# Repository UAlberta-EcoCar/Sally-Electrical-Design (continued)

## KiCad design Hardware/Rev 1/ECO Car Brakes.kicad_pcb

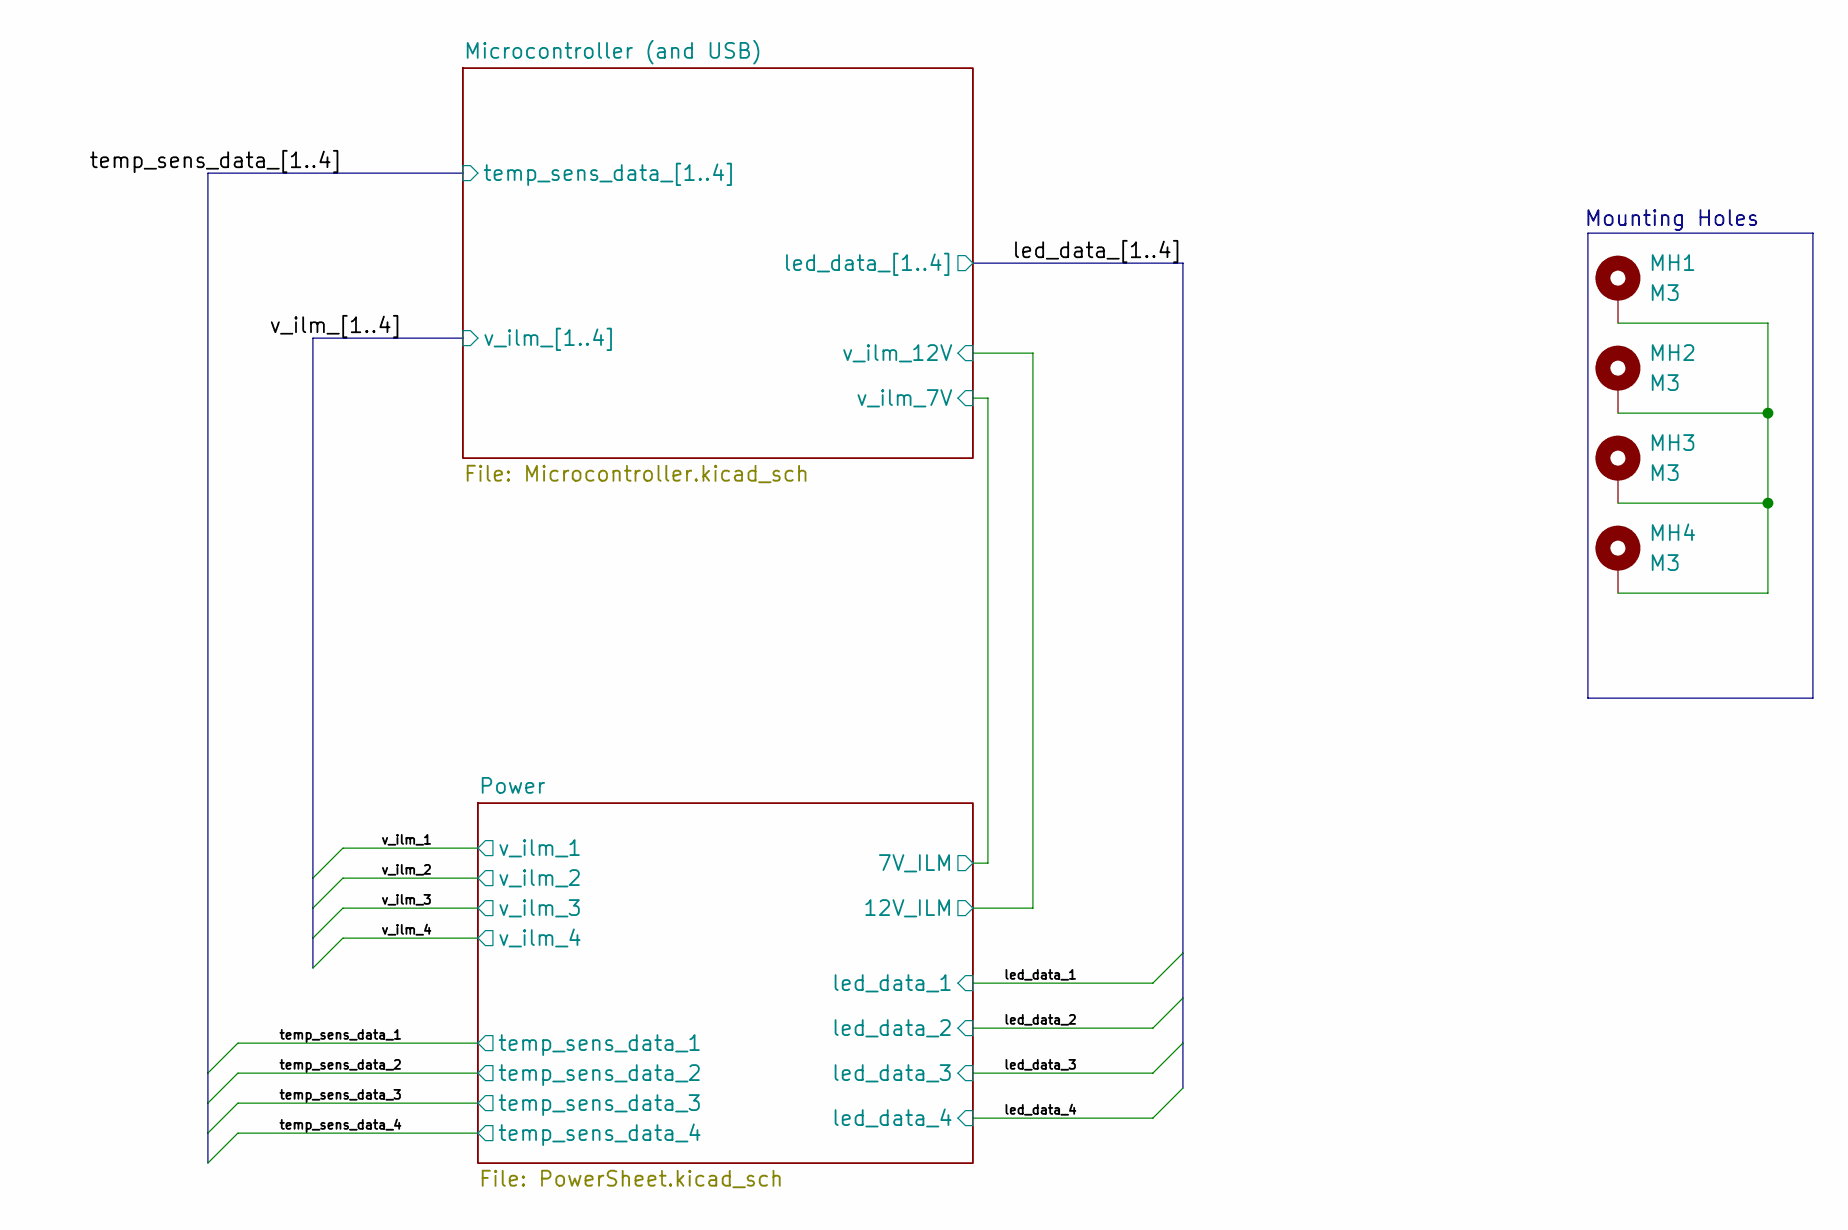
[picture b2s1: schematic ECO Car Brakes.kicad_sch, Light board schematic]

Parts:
MH1, MH2, MH3, MH4: M3; MountingHole_3.2mm_M3_Pad_Via

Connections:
unnamed: MH1.1 (1_1), MH2.1 (1_1), MH3.1 (1_1), MH4.1 (1_1)

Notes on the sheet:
Mounting Holes

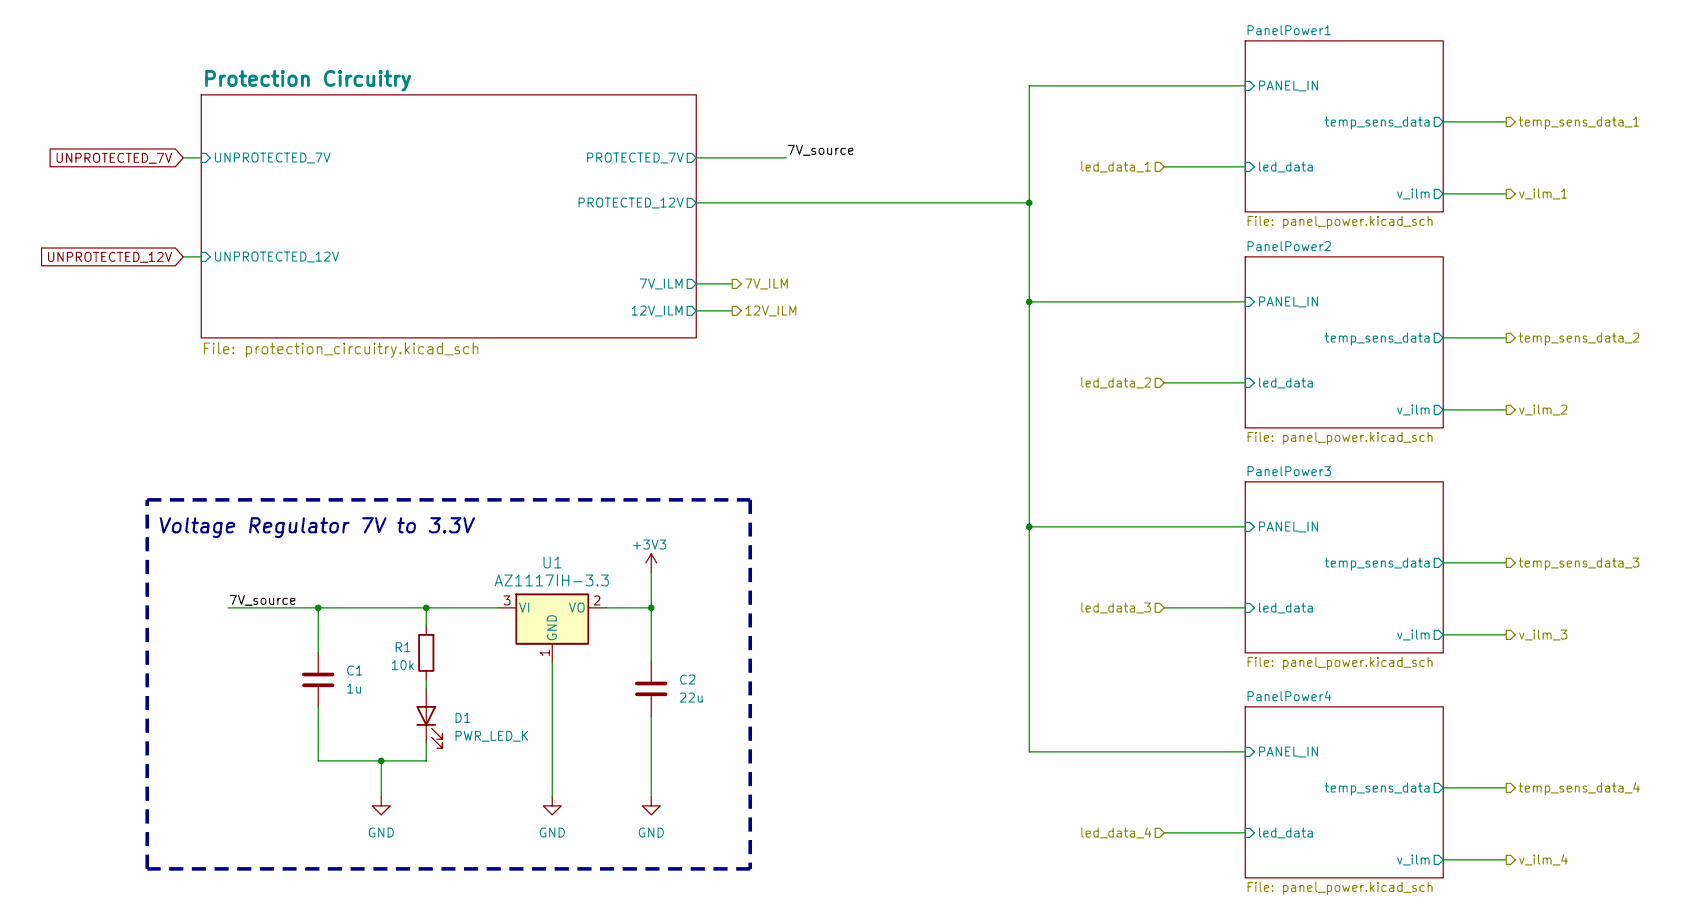
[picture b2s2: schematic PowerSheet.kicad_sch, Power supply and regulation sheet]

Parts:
C1: 1u; C_0603_1608Metric
C2: 22u; C_0603_1608Metric
D1: PWR_LED_K; LED_0805_2012Metric
R1: 10k; R_0603_1608Metric
U1: AZ1117IH-3.3; SOT-223-3_TabPin2

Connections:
+3V3: C2.1, U1.2 (VO); also elsewhere on the board
/Power/7V_source: C1.1, R1.2, U1.3 (VI); also elsewhere on the board
GND: C1.2, C2.2, D1.1 (K), U1.1 (GND); also elsewhere on the board
unnamed: D1.2 (A), R1.1

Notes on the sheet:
Voltage Regulator 7V to 3.3V

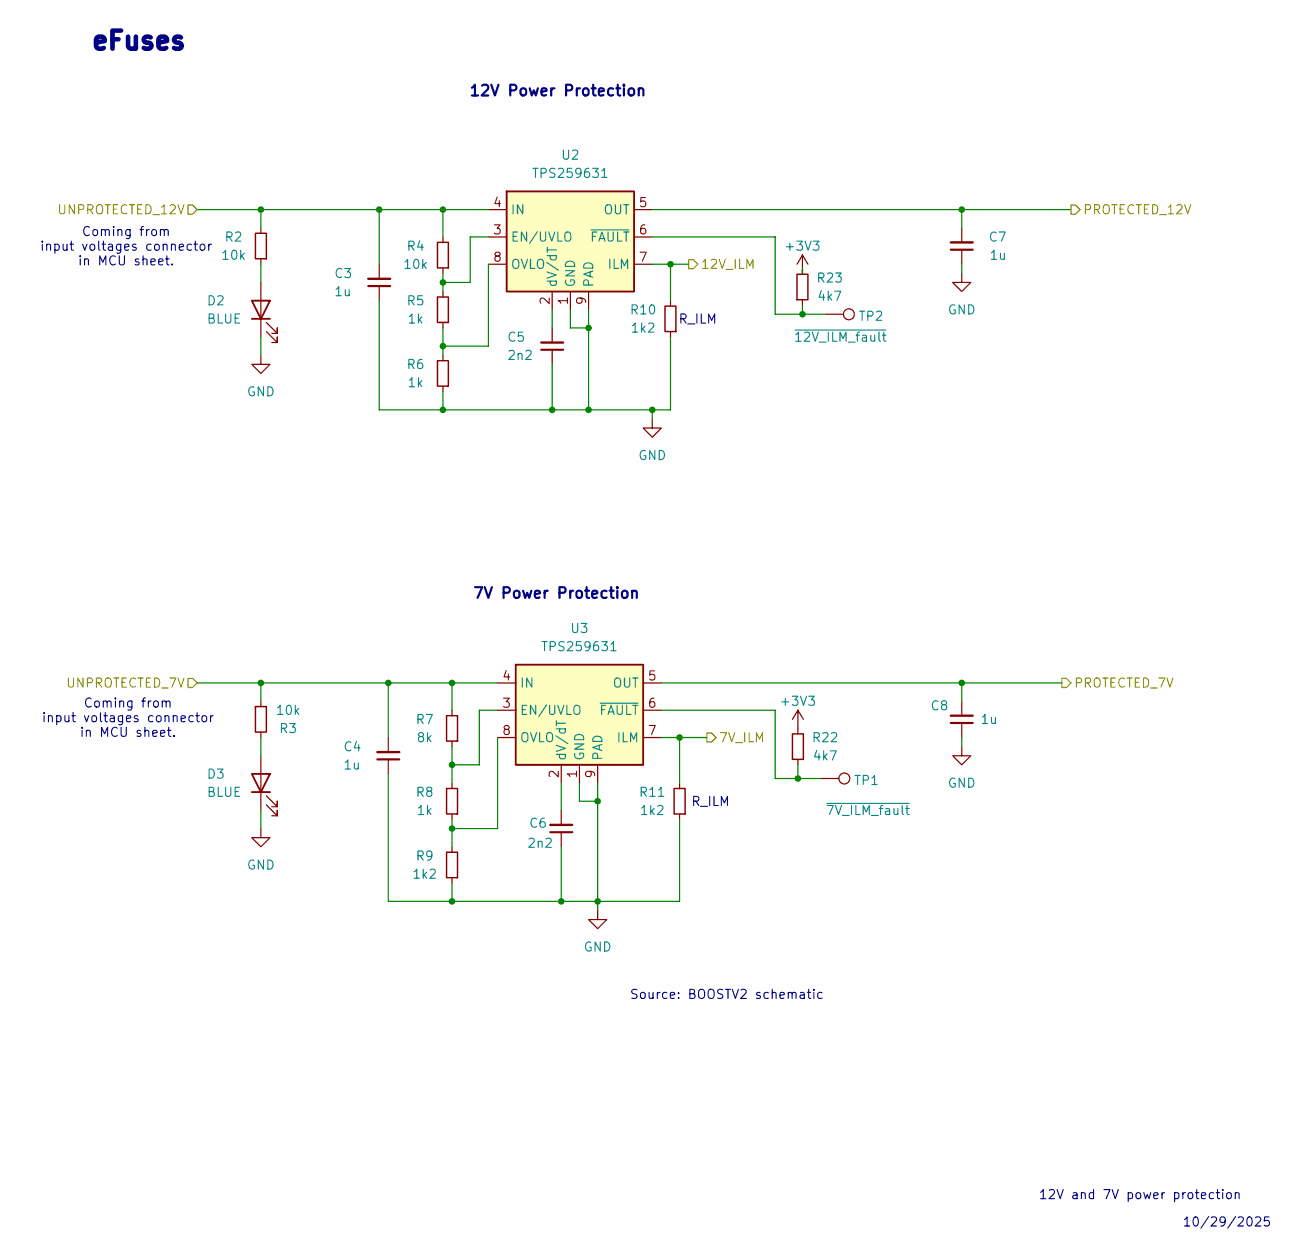
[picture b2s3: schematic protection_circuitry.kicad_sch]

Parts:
C3, C4, C7, C8: 1u; C_0603_1608Metric; Part# C15849
C5, C6: 2n2; C_0603_1608Metric; Part# C1604
D2, D3: BLUE; LED_0805_2012Metric; Part# C72041
R2: 10k; R_0603_1608Metric; Part# C23253
R3: 10k; R_0603_1608Metric; Part# C22966
R4: 10k; R_0603_1608Metric
R5, R6, R8: 1k; R_0603_1608Metric
R7: 8k; R_0603_1608Metric
R9, R10, R11: 1k2; R_0603_1608Metric
R22, R23: 4k7; R_0603_1608Metric
TP1: ~{7V_ILM_fault}; TestPoint_Pad_2.0x2.0mm
TP2: ~{12V_ILM_fault}; TestPoint_Pad_2.0x2.0mm
U2, U3: TPS259631; TI_SO-PowerPAD-8

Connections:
+3V3: R22.2, R23.2; also elsewhere on the board
/Microcontroller (and USB)/v_ilm_7V: R11.2, U3.7 (ILM); also elsewhere on the board
/Microcontroller (and USB)/v_ilm_12V: R10.2, U2.7 (ILM); also elsewhere on the board
/Power/7V_source: C8.2, U3.5 (OUT); also elsewhere on the board
/Power/PanelPower1/PANEL_IN: C7.2, U2.5 (OUT); also elsewhere on the board
GND: C3.1, C4.1, C5.1, C6.1, C7.1, C8.1, D2.1 (K), D3.1 (K), R6.1, R9.1, R10.1, R11.1, U2.1 (GND), U2.9 (PAD), U3.1 (GND), U3.9 (PAD); also elsewhere on the board
unnamed: D2.2 (A), R2.1
unnamed: D3.2 (A), R3.2
unnamed: R4.1, R5.2, U2.3 (EN/UVLO)
unnamed: R5.1, R6.2, U2.8 (OVLO)
unnamed: C5.2, U2.2 (dV/dT)
unnamed: R23.1, TP2.1 (1_1), U2.6 (~FAULT)
unnamed: R7.1, R8.2, U3.3 (EN/UVLO)
unnamed: R8.1, R9.2, U3.8 (OVLO)
unnamed: C6.2, U3.2 (dV/dT)
unnamed: R22.1, TP1.1 (1_1), U3.6 (~FAULT)
UNPROTECTED_7V: C4.2, R3.1, R7.2, U3.4 (IN); also elsewhere on the board
UNPROTECTED_12V: C3.2, R2.2, R4.2, U2.4 (IN); also elsewhere on the board

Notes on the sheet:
10/29/2025
R_ILM
eFuses
12V Power Protection
Coming from input voltages connector in MCU sheet.
12V and 7V power protection
Source: BOOSTV2 schematic
7V Power Protection

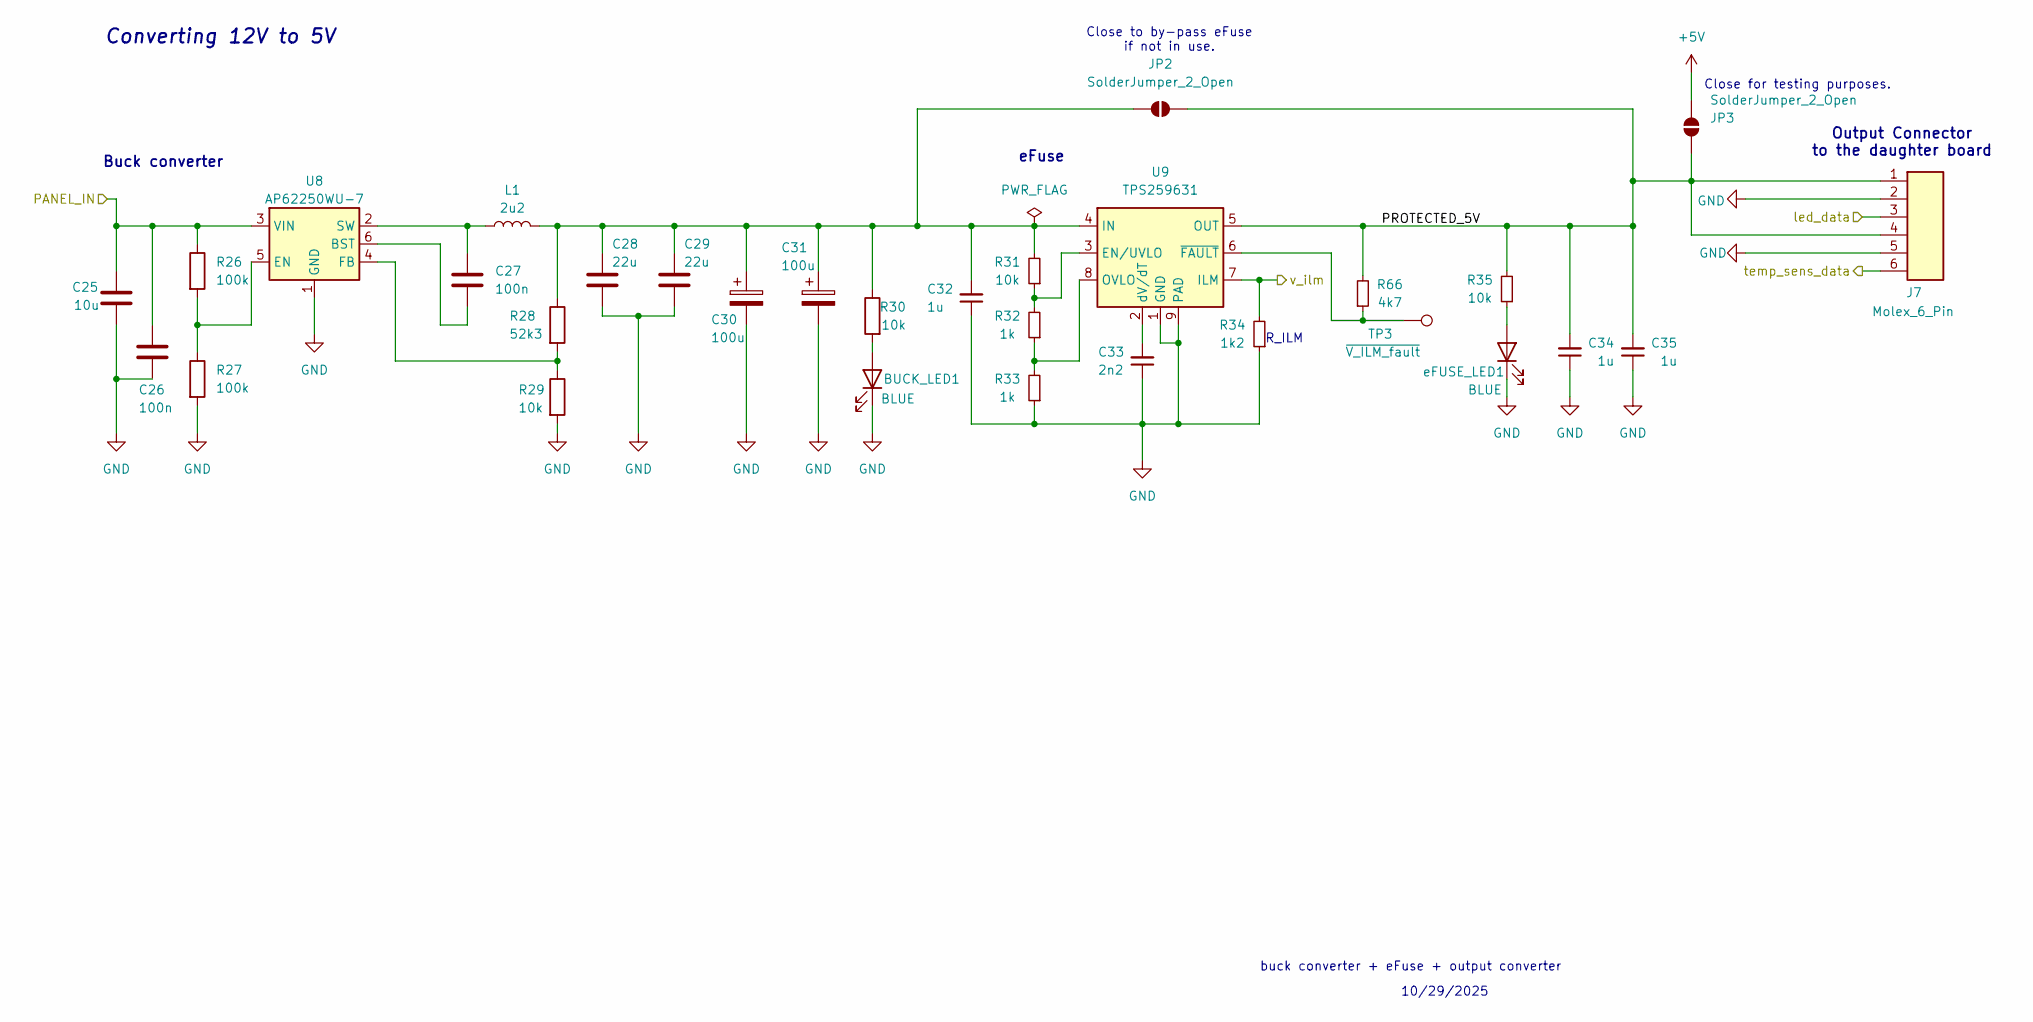
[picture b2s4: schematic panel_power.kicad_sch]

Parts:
BUCK_LED1: BLUE; LED_0805_2012Metric; Digikey # 160-1647-1-ND
C25: 10u; C_0603_1608Metric
C26, C27: 100n; C_0603_1608Metric; Digikey # CC0603KRX7R7BB104
C28, C29: 22u; C_0603_1608Metric
C30, C31: 100u; CP_Elec_6.3x7.7; Digikey # P10387TB-ND
C32, C34, C35: 1u; C_0603_1608Metric; Part# C15849
C33: 2n2; C_0603_1608Metric; Part# C1604
J7: Molex_6_Pin; Molex_6_Pin_FTP
JP2, JP3: SolderJumper_2_Open; SolderJumper-2_P1.3mm_Open_RoundedPad1.0x1.5mm
L1: 2u2; L_0603_1608Metric; Digikey # 732-13496-1-ND
R26, R27: 100k; R_0603_1608Metric
R28: 52k3; R_0603_1608Metric; Digikey # RMCF0603FT52K3CT-ND
R29: 10k; R_0603_1608Metric; Digikey # RMCF0603FT52K3CT-ND
R30: 10k; R_0603_1608Metric; JLCPCB Part#(Optional) C28636
R31: 10k; R_0603_1608Metric
R32, R33: 1k; R_0603_1608Metric
R34: 1k2; R_0603_1608Metric
R35: 10k; R_0603_1608Metric; Part# C23253
R66: 4k7; R_0603_1608Metric
TP3: ~{V_ILM_fault}; TestPoint_Pad_2.0x2.0mm
U8: AP62250WU-7; TSOT-23-6
U9: TPS259631; TI_SO-PowerPAD-8
eFUSE_LED1: BLUE; LED_0805_2012Metric; Part# C72041

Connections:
+5V: JP3.2 (B); also elsewhere on the board
/Power/PanelPower1/PANEL_IN: C25.1, C26.1, R26.1, U8.3 (VIN); also elsewhere on the board
/Power/PanelPower1/PROTECTED_5V: C34.2, C35.2, J7.1, J7.4, JP2.2 (B), JP3.1 (A), R35.2, R66.2, U9.5 (OUT)
/led_data_1: J7.3; also elsewhere on the board
/temp_sens_data_1: J7.6; also elsewhere on the board
/v_ilm_1: R34.2, U9.7 (ILM); also elsewhere on the board
GND: BUCK_LED1.1 (K), C25.2, C26.2, C28.2, C29.2, C30.2, C31.2, C32.1, C33.1, C34.1, C35.1, J7.2, J7.5, R27.2, R29.2, R33.1, R34.1, U8.1 (GND), U9.1 (GND), U9.9 (PAD), eFUSE_LED1.1 (K); also elsewhere on the board
unnamed 45: R30.2; also elsewhere on the board
unnamed: C28.1, C29.1, C30.1, C31.1, C32.2, JP2.1 (A), L1.2, R28.1, R30.1, R31.2, U9.4 (IN)
unnamed: C27.2, U8.6 (BST)
unnamed: R26.2, R27.1, U8.5 (EN)
unnamed: R28.2, R29.1, U8.4 (FB)
unnamed: C27.1, L1.1, U8.2 (SW)
unnamed: R31.1, R32.2, U9.3 (EN/UVLO)
unnamed: R32.1, R33.2, U9.8 (OVLO)
unnamed: C33.2, U9.2 (dV/dT)
unnamed: R66.1, TP3.1 (1_1), U9.6 (~FAULT)
unnamed: R35.1, eFUSE_LED1.2 (A)

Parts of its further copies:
C36, C47, C58: 10u; C_0603_1608Metric
C37, C38, C48, C49, C59, C60: 100n; C_0603_1608Metric; Digikey # CC0603KRX7R7BB104
C39, C40, C50, C51, C61, C62: 22u; C_0603_1608Metric
C41, C42, C52, C53, C63, C64: 100u; CP_Elec_6.3x7.7; Digikey # P10387TB-ND
C43, C45, C46, C54, C56, C57, C65, C67, C68: 1u; C_0603_1608Metric; Part# C15849
C44, C55, C66: 2n2; C_0603_1608Metric; Part# C1604
J8, J9, J10: Molex_6_Pin; Molex_6_Pin_FTP
JP4, JP5, JP6, JP7, JP8, JP9: SolderJumper_2_Open; SolderJumper-2_P1.3mm_Open_RoundedPad1.0x1.5mm
L2, L3, L4: 2u2; L_0603_1608Metric; Digikey # 732-13496-1-ND
R36, R37, R46, R47, R56, R57: 100k; R_0603_1608Metric
R38, R48, R58: 52k3; R_0603_1608Metric; Digikey # RMCF0603FT52K3CT-ND
R39, R49, R59: 10k; R_0603_1608Metric; Digikey # RMCF0603FT52K3CT-ND
R40, R50, R60: 10k; R_0603_1608Metric; JLCPCB Part#(Optional) C28636
R41, R51, R61: 10k; R_0603_1608Metric
R42, R43, R52, R53, R62, R63: 1k; R_0603_1608Metric
R44, R54, R64: 1k2; R_0603_1608Metric
R45, R55, R65: 10k; R_0603_1608Metric; Part# C23253
R67, R68, R69: 4k7; R_0603_1608Metric
TP4, TP5, TP6: ~{V_ILM_fault}; TestPoint_Pad_2.0x2.0mm
U10, U12, U14: AP62250WU-7; TSOT-23-6
U11, U13, U15: TPS259631; TI_SO-PowerPAD-8
eFUSE_LED2: BLUE; LED_0805_2012Metric; Part# C72041

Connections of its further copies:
+5V: JP5.2 (B), JP7.2 (B), JP9.2 (B); also elsewhere on the board
/Power/PanelPower1/PANEL_IN: C36.1, C37.1, C47.1, C48.1, C58.1, C59.1, R36.1, R46.1, R56.1, U10.3 (VIN), U12.3 (VIN), U14.3 (VIN); also elsewhere on the board
/Power/PanelPower2/PROTECTED_5V: C45.2, C46.2, J8.1, J8.4, JP4.2 (B), JP5.1 (A), R45.2, R67.2, U11.5 (OUT)
/Power/PanelPower3/PROTECTED_5V: C56.2, C57.2, J9.1, J9.4, JP6.2 (B), JP7.1 (A), R55.2, R68.2, U13.5 (OUT)
/Power/PanelPower4/PROTECTED_5V: C67.2, C68.2, J10.1, J10.4, JP8.2 (B), JP9.1 (A), R65.2, R69.2, U15.5 (OUT)
/led_data_2: J8.3; also elsewhere on the board
/led_data_3: J9.3; also elsewhere on the board
/led_data_4: J10.3; also elsewhere on the board
/temp_sens_data_2: J8.6; also elsewhere on the board
/temp_sens_data_3: J9.6; also elsewhere on the board
/temp_sens_data_4: J10.6; also elsewhere on the board
/v_ilm_2: R44.2, U11.7 (ILM); also elsewhere on the board
/v_ilm_3: R54.2, U13.7 (ILM); also elsewhere on the board
/v_ilm_4: R64.2, U15.7 (ILM); also elsewhere on the board
GND: C36.2, C37.2, C39.2, C40.2, C41.2, C42.2, C43.1, C44.1, C45.1, C46.1, C47.2, C48.2, C50.2, C51.2, C52.2, C53.2, C54.1, C55.1, C56.1, C57.1, C58.2, C59.2, C61.2, C62.2, C63.2, C64.2, C65.1, C66.1, C67.1, C68.1, J8.2, J8.5, J9.2, J9.5, J10.2, J10.5, R37.2, R39.2, R43.1, R44.1, R47.2, R49.2, R53.1, R54.1, R57.2, R59.2, R63.1, R64.1, U10.1 (GND), U11.1 (GND), U11.9 (PAD), U12.1 (GND), U13.1 (GND), U13.9 (PAD), U14.1 (GND), U15.1 (GND), U15.9 (PAD), eFUSE_LED2.1 (K); also elsewhere on the board
unnamed 46: R40.2; also elsewhere on the board
unnamed 47: R50.2; also elsewhere on the board
unnamed 48: R60.2; also elsewhere on the board
unnamed: C39.1, C40.1, C41.1, C42.1, C43.2, JP4.1 (A), L2.2, R38.1, R40.1, R41.2, U11.4 (IN)
unnamed: C50.1, C51.1, C52.1, C53.1, C54.2, JP6.1 (A), L3.2, R48.1, R50.1, R51.2, U13.4 (IN)
unnamed: C61.1, C62.1, C63.1, C64.1, C65.2, JP8.1 (A), L4.2, R58.1, R60.1, R61.2, U15.4 (IN)
unnamed: C38.2, U10.6 (BST)
unnamed: R36.2, R37.1, U10.5 (EN)
unnamed: R38.2, R39.1, U10.4 (FB)
unnamed: C38.1, L2.1, U10.2 (SW)
unnamed: R41.1, R42.2, U11.3 (EN/UVLO)
unnamed: R42.1, R43.2, U11.8 (OVLO)
unnamed: C44.2, U11.2 (dV/dT)
unnamed: R67.1, TP4.1 (1_1), U11.6 (~FAULT)
unnamed: C49.2, U12.6 (BST)
unnamed: R46.2, R47.1, U12.5 (EN)
unnamed: R48.2, R49.1, U12.4 (FB)
unnamed: C49.1, L3.1, U12.2 (SW)
unnamed: R51.1, R52.2, U13.3 (EN/UVLO)
unnamed: R52.1, R53.2, U13.8 (OVLO)
unnamed: C55.2, U13.2 (dV/dT)
unnamed: R68.1, TP5.1 (1_1), U13.6 (~FAULT)
unnamed: C60.2, U14.6 (BST)
unnamed: R56.2, R57.1, U14.5 (EN)
unnamed: R58.2, R59.1, U14.4 (FB)
unnamed: C60.1, L4.1, U14.2 (SW)
unnamed: R61.1, R62.2, U15.3 (EN/UVLO)
unnamed: R62.1, R63.2, U15.8 (OVLO)
unnamed: C66.2, U15.2 (dV/dT)
unnamed: R69.1, TP6.1 (1_1), U15.6 (~FAULT)
unnamed: R45.1, eFUSE_LED2.2 (A)
unnamed 110: R55.1; also elsewhere on the board
unnamed 111: R65.1; also elsewhere on the board

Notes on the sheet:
buck converter + eFuse + output converter
Buck converter
Converting 12V to 5V
Close for testing purposes.
Output Connector to the daughter board
eFuse
R_ILM
Close to by-pass eFuse if not in use.
10/29/2025

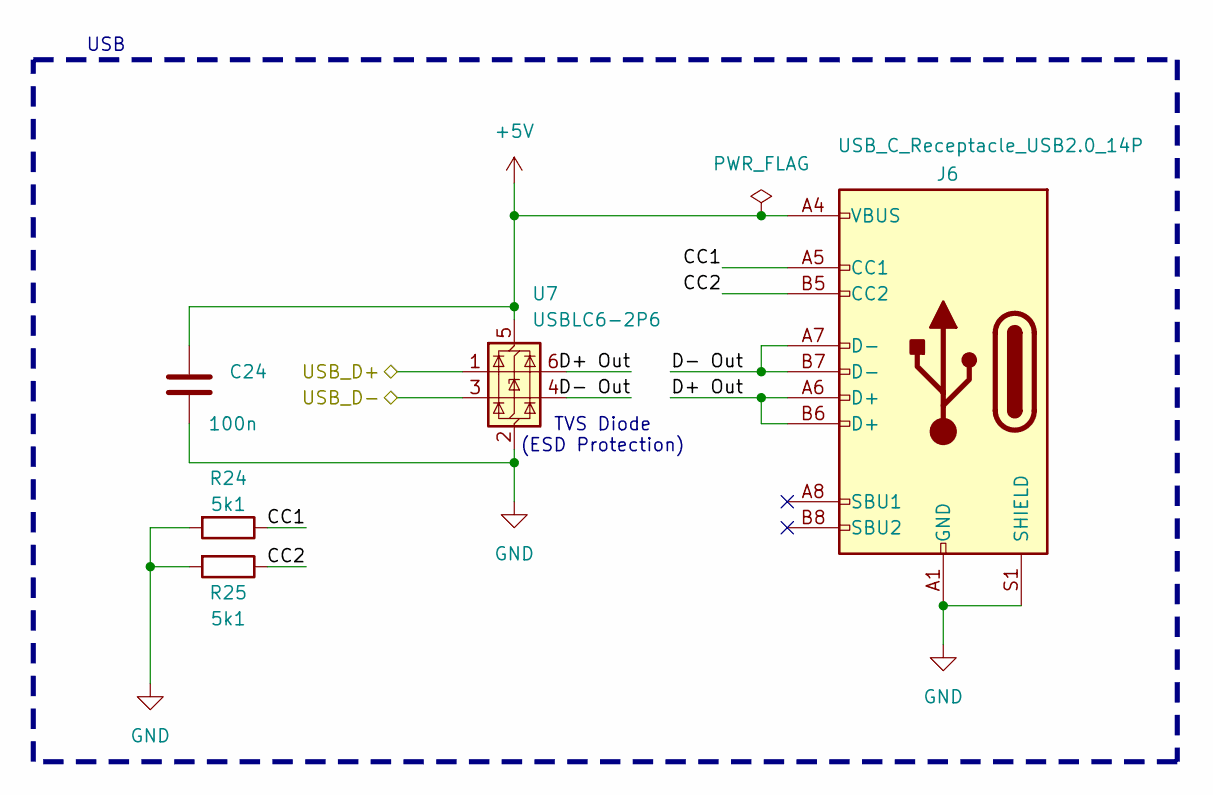
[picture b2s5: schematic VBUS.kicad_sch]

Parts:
C24: 100n; C_0603_1608Metric
J6: USB_C_Receptacle_USB2.0_14P; USB_C_Receptacle_HRO_TYPE-C-31-M-12
R24, R25: 5k1; R_0603_1608Metric
U7: USBLC6-2P6; SOT-666

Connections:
+5V: C24.1, J6.A4 (VBUS), J6.A9 (VBUS), J6.B4 (VBUS), J6.B9 (VBUS), U7.5 (VBUS); also elsewhere on the board
/Microcontroller (and USB)/MCU/USB_D+: U7.1 (I/O1); also elsewhere on the board
/Microcontroller (and USB)/MCU/USB_D-: U7.3 (I/O2); also elsewhere on the board
/Microcontroller (and USB)/VBUS/CC1: J6.A5 (CC1), R24.1
/Microcontroller (and USB)/VBUS/CC2: J6.B5 (CC2), R25.1
/Microcontroller (and USB)/VBUS/D+ Out: J6.A6 (D+), J6.B6 (D+), U7.6 (I/O1)
/Microcontroller (and USB)/VBUS/D- Out: J6.A7 (D-), J6.B7 (D-), U7.4 (I/O2)
GND: C24.2, J6.A1 (GND), J6.A12 (GND), J6.B1 (GND), J6.B12 (GND), J6.S1 (SHIELD), R24.2, R25.2, U7.2 (GND); also elsewhere on the board

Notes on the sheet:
USB
TVS Diode (ESD Protection)

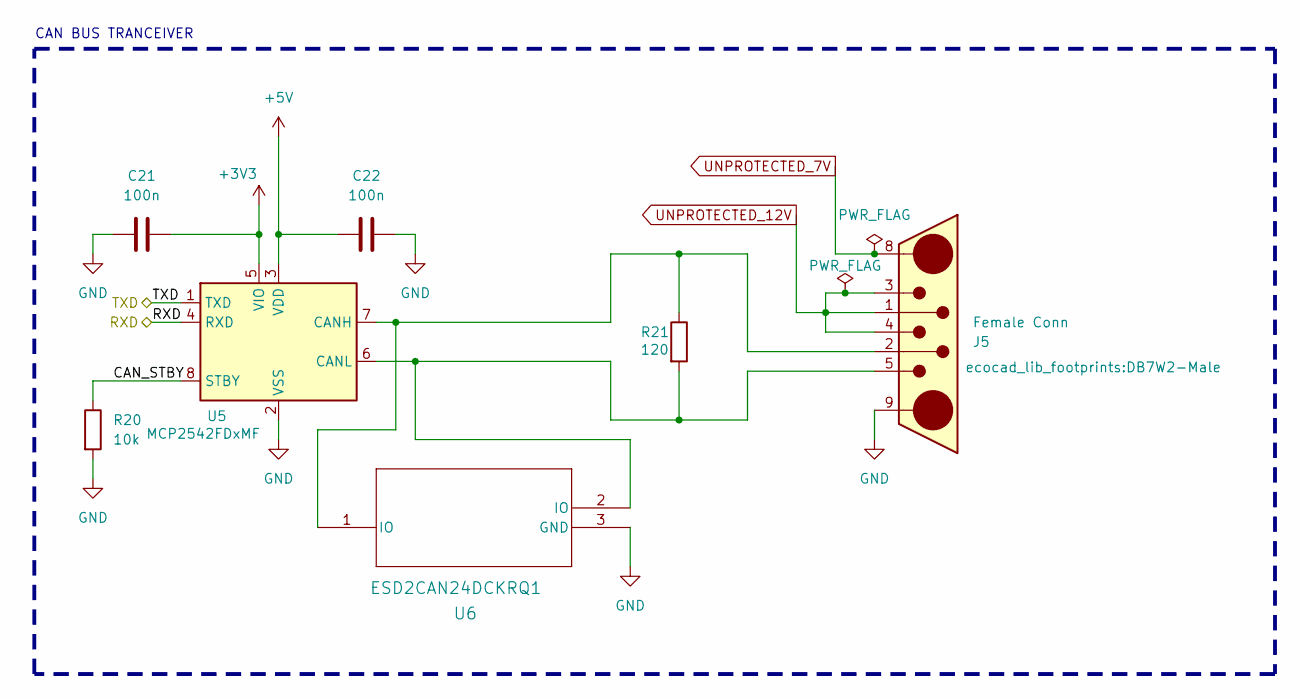
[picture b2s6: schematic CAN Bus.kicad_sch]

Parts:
C21, C22: 100n; C_0603_1608Metric
J5: Female Conn; DB7W2-Male
R20: 10k; R_0603_1608Metric
R21: 120; R_0603_1608Metric
U5: MCP2542FDxMF; DFN-8-1EP_3x3mm_P0.65mm_EP1.55x2.4mm
U6: ESD2CAN24DCKRQ1; SOT-SC70_3_DCK_TEX

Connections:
+3V3: C21.2, U5.5 (VIO); also elsewhere on the board
+5V: C22.1, U5.3 (VDD); also elsewhere on the board
/Microcontroller (and USB)/CAN Bus/CAN_STBY: R20.1, U5.8 (STBY)
/Microcontroller (and USB)/CAN Bus/RXD: U5.4 (RXD); also elsewhere on the board
/Microcontroller (and USB)/CAN Bus/TXD: U5.1 (TXD); also elsewhere on the board
GND: C21.1, C22.2, J5.9, R20.2, U5.2 (VSS), U5.9 (VSS), U6.3 (GND); also elsewhere on the board
unnamed: J5.2, R21.1, U5.7 (CANH), U6.1 (IO)
unnamed: J5.5, R21.2, U5.6 (CANL), U6.2 (IO)
UNPROTECTED_7V: J5.8; also elsewhere on the board
UNPROTECTED_12V: J5.1, J5.3, J5.4; also elsewhere on the board

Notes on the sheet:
CAN BUS TRANCEIVER

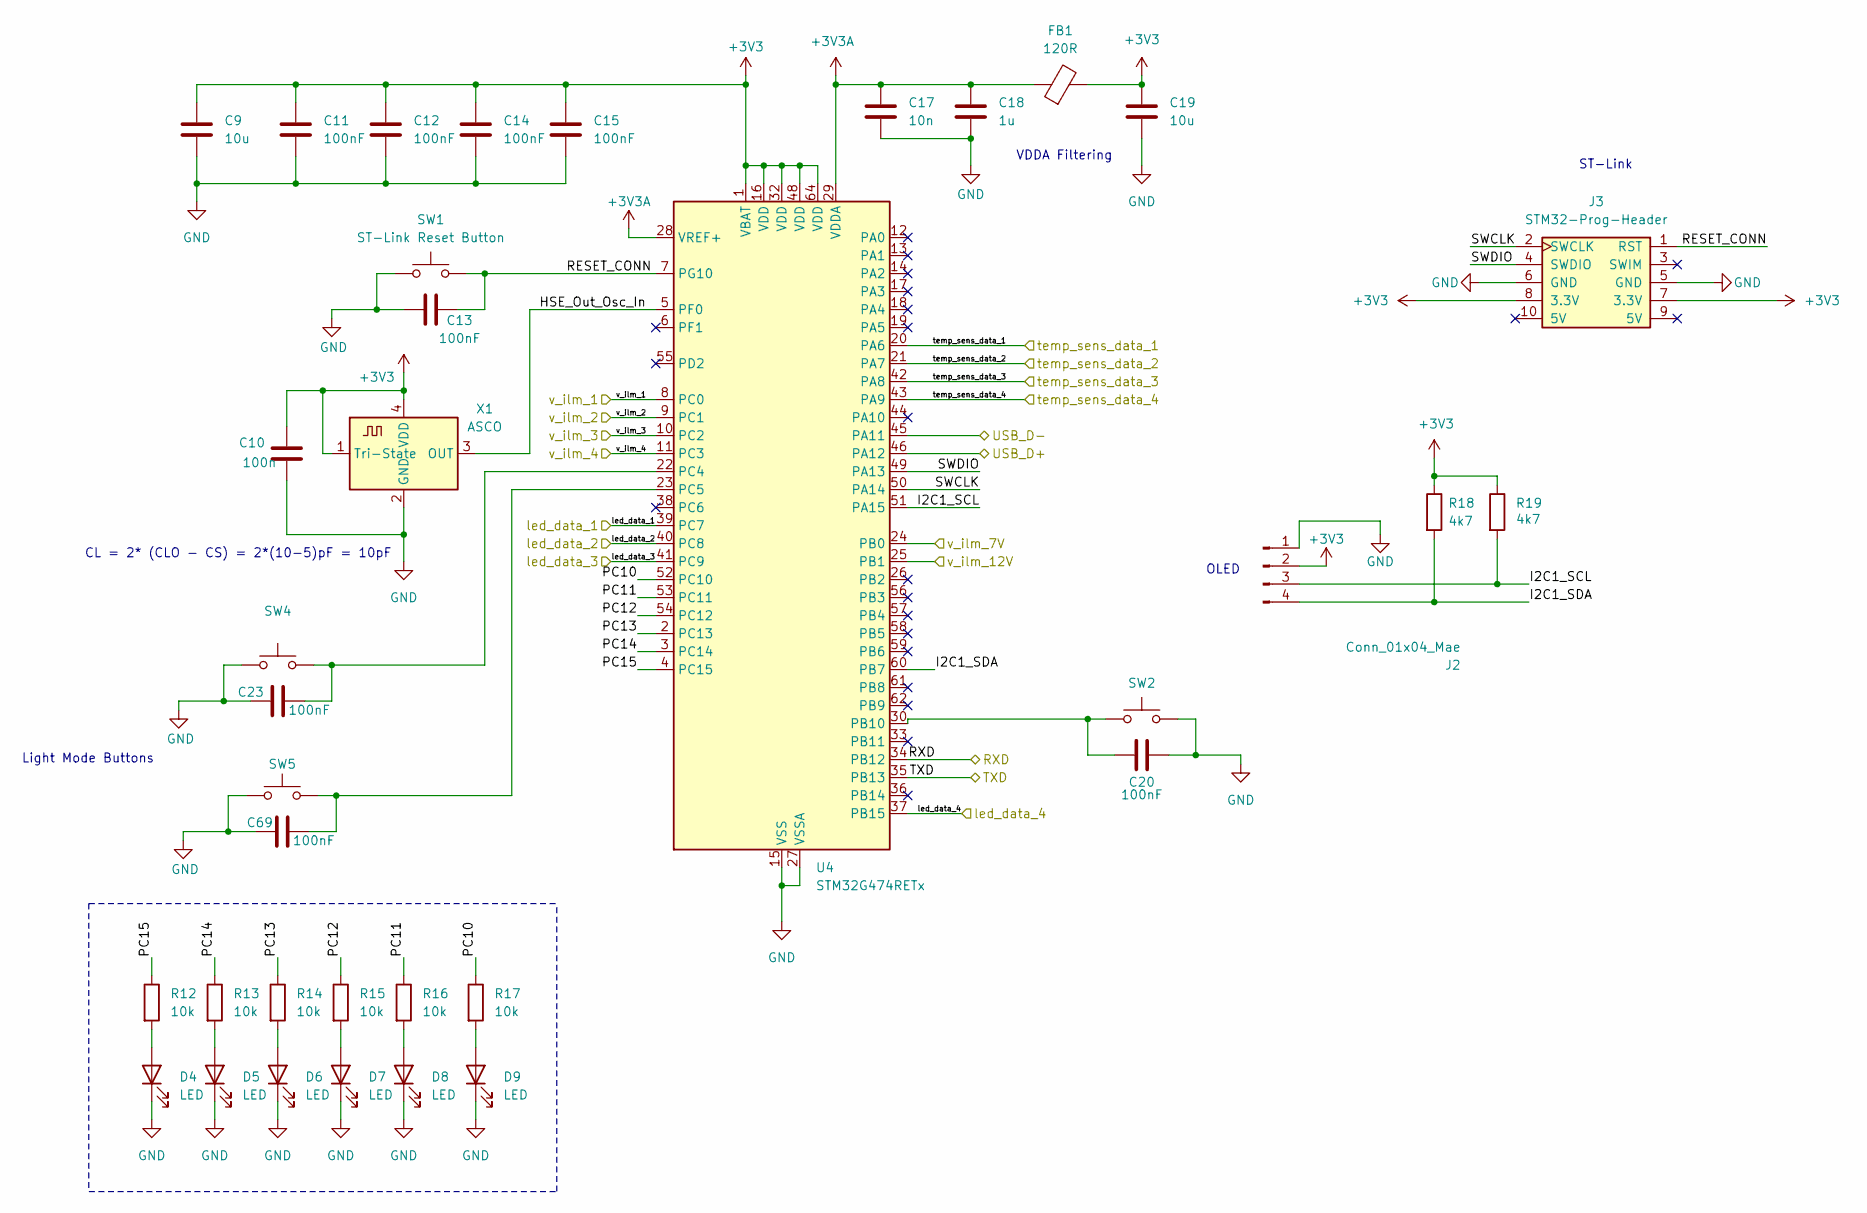
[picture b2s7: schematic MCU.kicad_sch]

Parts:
C9, C19: 10u; C_0603_1608Metric
C10: 100n; C_0603_1608Metric
C11, C12, C13, C14, C15, C20, C23, C69: 100nF; C_0603_1608Metric
C17: 10n; C_0603_1608Metric
C18: 1u; C_0603_1608Metric
D4, D5, D6, D7, D8, D9: LED; LED_0805_2012Metric
FB1: 120R; L_0603_1608Metric
J2: Conn_01x04_Mae; PinHeader_1x04_P2.54mm_Vertical
J3: STM32-Prog-Header; IDC-STM32-Prog-Header_2x05_P2.54mm_Vertical
R12, R13, R14, R15, R16, R17: 10k; R_0603_1608Metric
R18, R19: 4k7; R_0402_1005Metric
SW1, SW4, SW5: ST-Link Reset Button; SW_SPST_PTS810
SW2: BOOT; SW_SPST_PTS810
U4: STM32G474RETx; LQFP-64_10x10mm_P0.5mm
X1: ASCO; Oscillator_SMD_Abracon_ASE-4Pin_3.2x2.5mm

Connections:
+3V3: C9.1, C10.1, C11.1, C12.1, C14.1, C15.1, C19.1, FB1.2, J2.2, J3.7 (3.3V), J3.8 (3.3V), R18.1, R19.1, U4.1 (VBAT), U4.16 (VDD), U4.32 (VDD), U4.48 (VDD), U4.64 (VDD), X1.1 (Tri-State), X1.4 (VDD); also elsewhere on the board
+3V3A: C17.1, C18.1, FB1.1, U4.28 (VREF+), U4.29 (VDDA)
/Microcontroller (and USB)/CAN Bus/RXD: U4.34 (PB12); also elsewhere on the board
/Microcontroller (and USB)/CAN Bus/TXD: U4.35 (PB13); also elsewhere on the board
/Microcontroller (and USB)/MCU/HSE_Out_Osc_In: U4.5 (PF0), X1.3 (OUT)
/Microcontroller (and USB)/MCU/I2C1_SCL: J2.3, R19.2, U4.51 (PA15)
/Microcontroller (and USB)/MCU/I2C1_SDA: J2.4, R18.2, U4.60 (PB7)
/Microcontroller (and USB)/MCU/PC10: R17.1, U4.52 (PC10)
/Microcontroller (and USB)/MCU/PC11: R16.1, U4.53 (PC11)
/Microcontroller (and USB)/MCU/PC12: R15.1, U4.54 (PC12)
/Microcontroller (and USB)/MCU/PC13: R14.1, U4.2 (PC13)
/Microcontroller (and USB)/MCU/PC14: R13.1, U4.3 (PC14)
/Microcontroller (and USB)/MCU/PC15: R12.1, U4.4 (PC15)
/Microcontroller (and USB)/MCU/RESET_CONN: C13.2, J3.1 (RST), SW1.2, U4.7 (PG10)
/Microcontroller (and USB)/MCU/SWCLK: J3.2 (SWCLK), U4.50 (PA14)
/Microcontroller (and USB)/MCU/SWDIO: J3.4 (SWDIO), U4.49 (PA13)
/Microcontroller (and USB)/MCU/USB_D+: U4.46 (PA12); also elsewhere on the board
/Microcontroller (and USB)/MCU/USB_D-: U4.45 (PA11); also elsewhere on the board
/Microcontroller (and USB)/v_ilm_7V: U4.24 (PB0); also elsewhere on the board
/Microcontroller (and USB)/v_ilm_12V: U4.25 (PB1); also elsewhere on the board
/led_data_1: U4.39 (PC7); also elsewhere on the board
/led_data_2: U4.40 (PC8); also elsewhere on the board
/led_data_3: U4.41 (PC9); also elsewhere on the board
/led_data_4: U4.37 (PB15); also elsewhere on the board
/temp_sens_data_1: U4.20 (PA6); also elsewhere on the board
/temp_sens_data_2: U4.21 (PA7); also elsewhere on the board
/temp_sens_data_3: U4.42 (PA8); also elsewhere on the board
/temp_sens_data_4: U4.43 (PA9); also elsewhere on the board
/v_ilm_1: U4.8 (PC0); also elsewhere on the board
/v_ilm_2: U4.9 (PC1); also elsewhere on the board
/v_ilm_3: U4.10 (PC2); also elsewhere on the board
/v_ilm_4: U4.11 (PC3); also elsewhere on the board
GND: C9.2, C10.2, C11.2, C12.2, C13.1, C14.2, C15.2, C17.2, C18.2, C19.2, C20.1, C23.1, C69.1, D4.1 (K), D5.1 (K), D6.1 (K), D7.1 (K), D8.1 (K), D9.1 (K), J2.1, J3.5 (GND), J3.6 (GND), SW1.1, SW2.1, SW4.1, SW5.1, U4.15 (VSS), U4.27 (VSSA), U4.31 (VSS), U4.47 (VSS), U4.63 (VSS), X1.2 (GND); also elsewhere on the board
unnamed: D4.2 (A), R12.2
unnamed: D5.2 (A), R13.2
unnamed: D6.2 (A), R14.2
unnamed: D7.2 (A), R15.2
unnamed: D8.2 (A), R16.2
unnamed: D9.2 (A), R17.2
unnamed: C20.2, SW2.2, U4.30 (PB10)
unnamed: C23.2, SW4.2, U4.22 (PC4)
unnamed: C69.2, SW5.2, U4.23 (PC5)

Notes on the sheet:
CL = 2* (CLO - CS) = 2*(10-5)pF = 10pF
ST-Link
OLED
VDDA Filtering
Light Mode Buttons

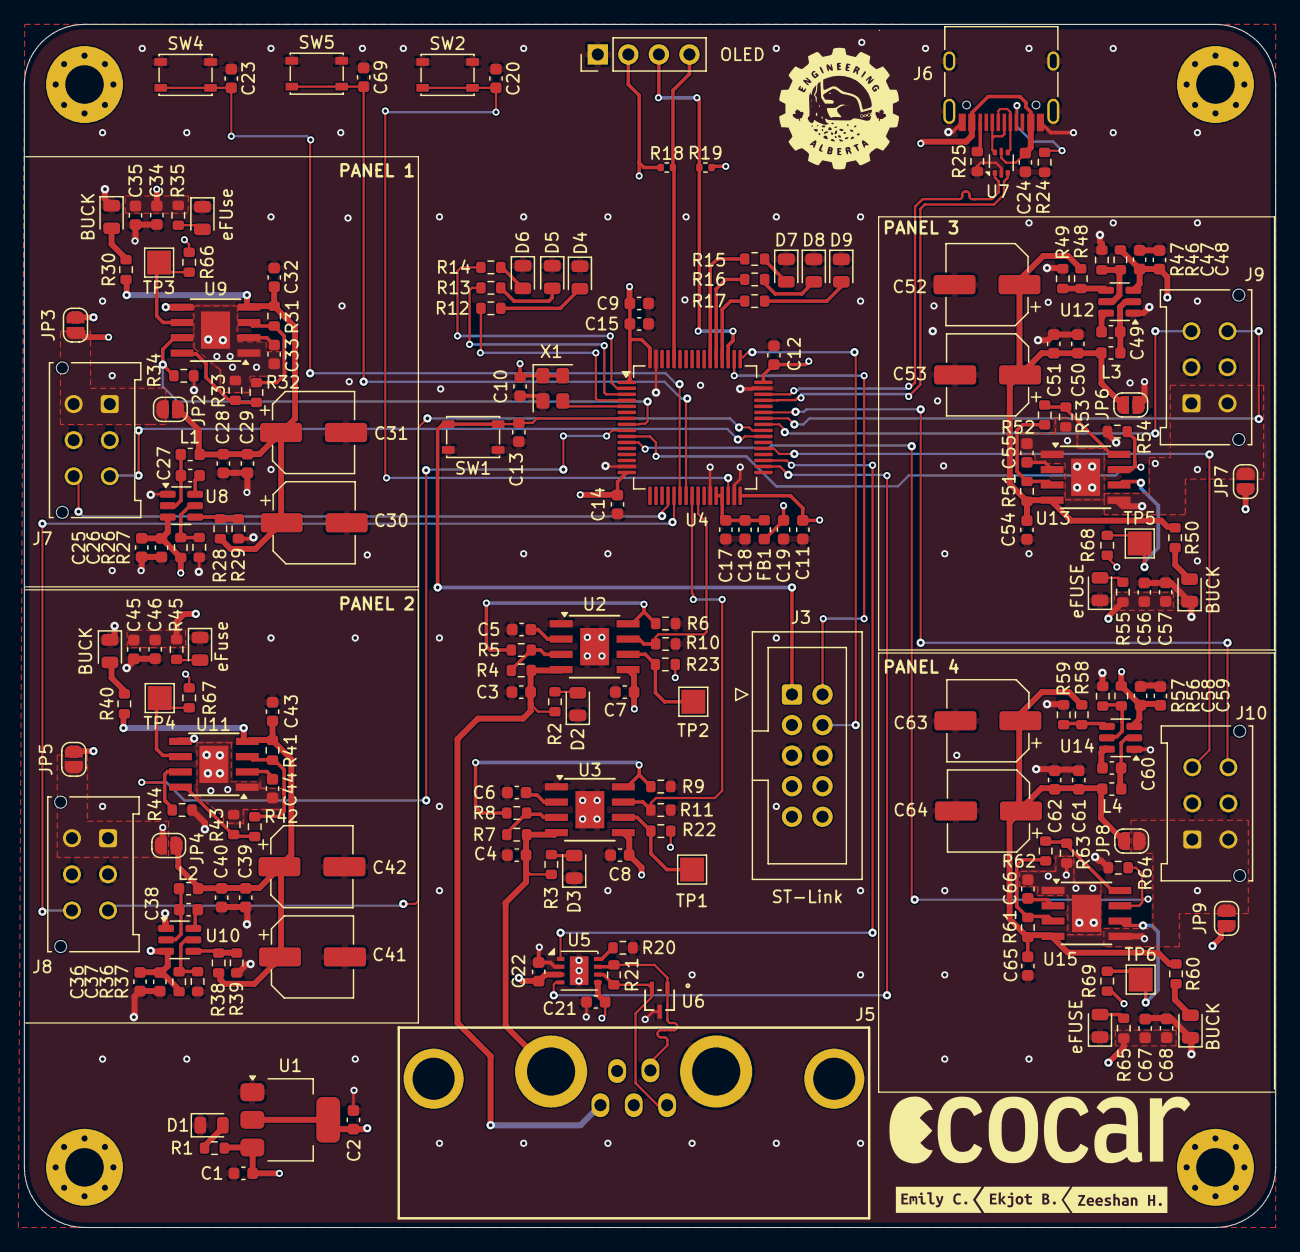
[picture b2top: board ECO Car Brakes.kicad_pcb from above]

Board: 4 copper layers, 104.0 x 100.0 mm, 208 parts (0 on the bottom side), 114 nets.

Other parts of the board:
BUCK: BLUE; LED_0805_2012Metric
BUCK#2, BUCK#3, BUCK#4: BLUE; LED_0805_2012Metric
eFUSE: BLUE; LED_0805_2012Metric
eFUSE#2: BLUE; LED_0805_2012Metric
kibuzzard-6A44278E: G***; kibuzzard-6A44278E
kibuzzard-6A44279E: G***; kibuzzard-6A44279E
kibuzzard-6A442853: G***; kibuzzard-6A442853

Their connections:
GND: BUCK.1 (K), BUCK#2.1 (K), BUCK#3.1 (K), BUCK#4.1 (K), eFUSE.1 (K), eFUSE#2.1 (K); also elsewhere on the board
unnamed 45: BUCK#3.2 (A); also elsewhere on the board
unnamed 46: BUCK#4.2 (A); also elsewhere on the board
unnamed 47: BUCK.2 (A); also elsewhere on the board
unnamed 48: BUCK#2.2 (A); also elsewhere on the board
unnamed 110: eFUSE#2.2 (A); also elsewhere on the board
unnamed 111: eFUSE.2 (A); also elsewhere on the board
